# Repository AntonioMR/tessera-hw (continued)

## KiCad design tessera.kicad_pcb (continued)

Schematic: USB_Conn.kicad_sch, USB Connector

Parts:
J1: USB-C; GCT_USB4520-03-1-A_REVA; Voltage 48VDC; Part Number USB4520-03-1-A_REVA
R15, R16: 510 kOhms; R_0402_1005Metric; Tolerance ±1%; Part Number R0402_510K_0.063W_±1%; not fitted
R17, R18: 5.1 kOhms; R_0402_1005Metric; Tolerance ±1%; Part Number R0402_5K1_0.063W_±1%
U1: USBLC6-2P6; SOT-666; Part Number USBLC6-2P6

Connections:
/Project Architecture/D+: U1.4 (I/O2); also elsewhere on the board
/Project Architecture/D-: U1.6 (I/O1); also elsewhere on the board
/Project Architecture/USB/USB_D+: J1.A6 (D+), J1.B6 (D+), U1.3 (I/O2)
/Project Architecture/USB/USB_D-: J1.A7 (D-), J1.B7 (D-), U1.1 (I/O1)
GND: J1.A1_B12 (GND), J1.B1_A12 (GND), J1.S1 (SHIELD), J1.S2 (SHIELD), J1.S3 (SHIELD), J1.S4 (SHIELD), R15.2, R16.2, R17.2, R18.2, U1.2 (GND); also elsewhere on the board
unnamed: J1.A5 (CC1), R18.1
unnamed: J1.B5 (CC2), R17.1
unnamed: J1.A8 (SBU1), R16.1
unnamed: J1.B8 (SBU2), R15.1
VBUS: J1.A4_B9 (VBUS), J1.B4_A9 (VBUS), U1.5 (VBUS); also elsewhere on the board

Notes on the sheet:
USB Interface / ESD protection
DESIGN NOTE: Mid-mount USB Type-C receptacle.
LAYOUT NOTE: 90 ohms differential impedance
[${#}] ${TITLE}
DESIGN NOTE: As close to the connector as possible

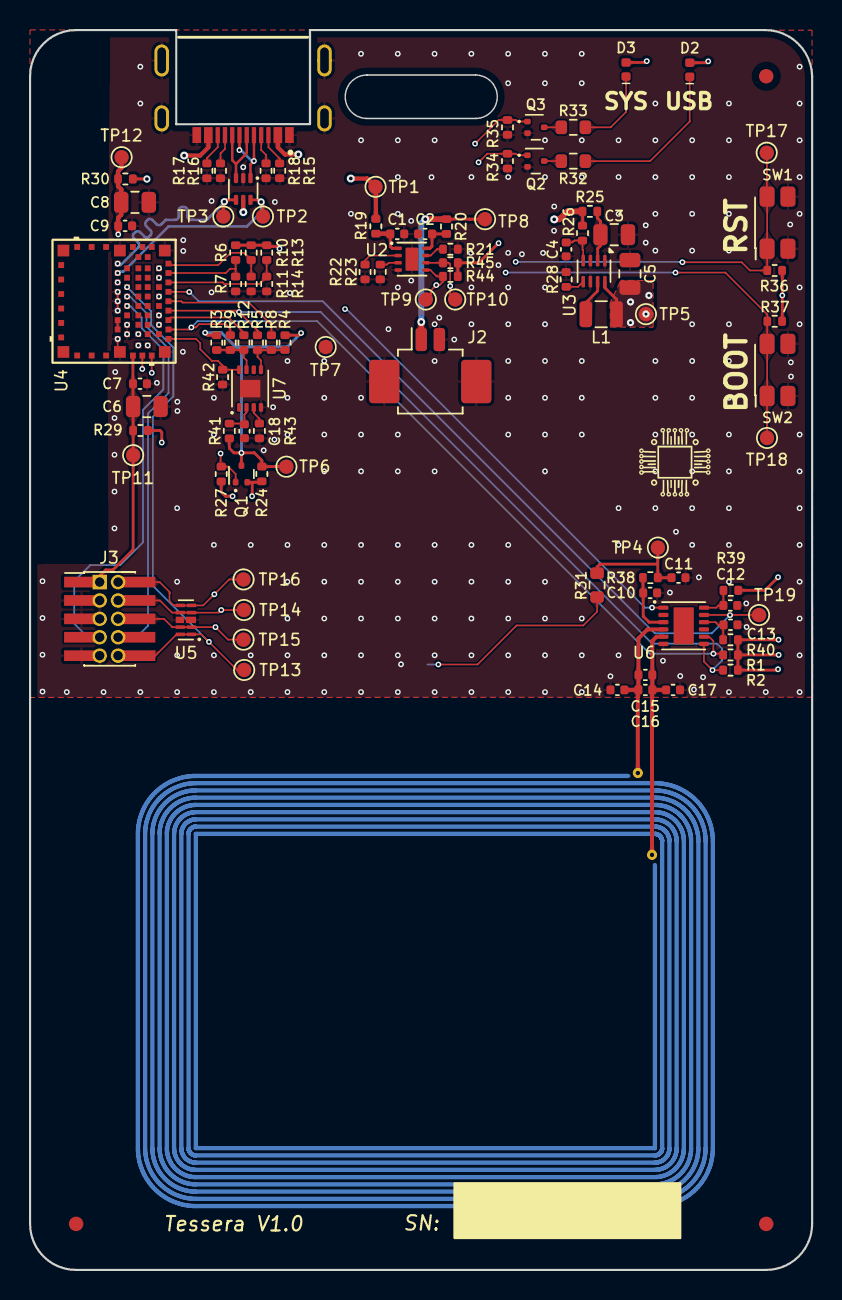
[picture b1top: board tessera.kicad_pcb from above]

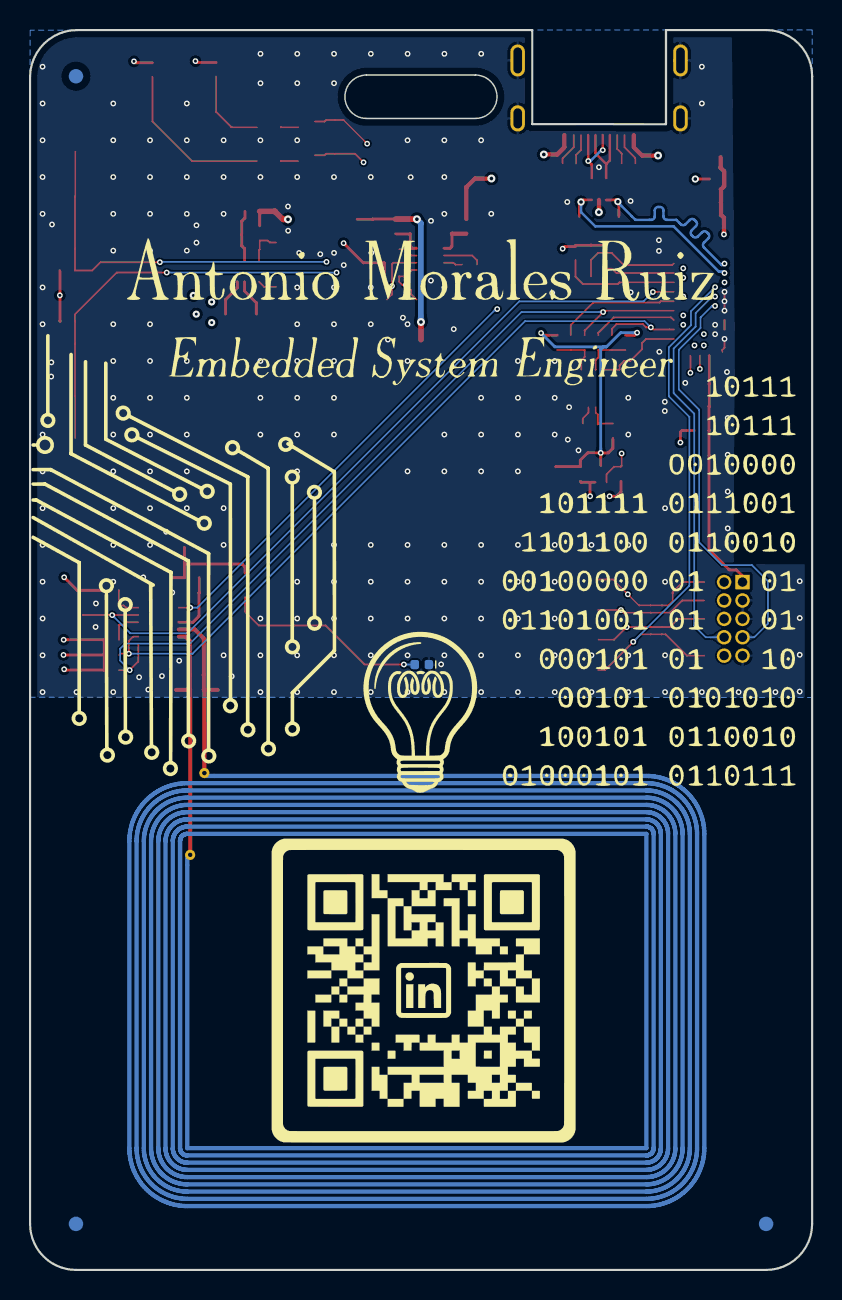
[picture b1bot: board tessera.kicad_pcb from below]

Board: 4 copper layers, 54.0 x 85.6 mm, 113 parts (9 on the bottom side), 62 nets.
